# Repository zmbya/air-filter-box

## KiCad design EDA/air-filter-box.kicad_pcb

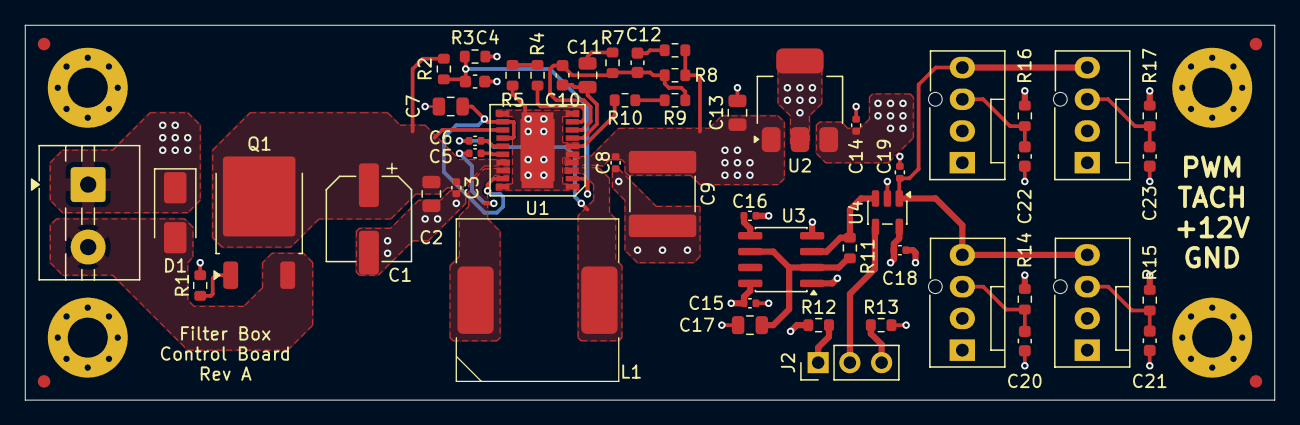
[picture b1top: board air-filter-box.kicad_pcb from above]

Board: 4 copper layers, 100.0 x 30.0 mm, 61 parts (0 on the bottom side), 30 nets.

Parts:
C1: 47u; CP_Elec_6.3x7.7
C2, C7, C13: 470n; C_0805_2012Metric
C3, C5, C6, C8, C14, C15, C16, C18, C19: 100n; C_0402_1005Metric
C4: 1n; C_0603_1608Metric
C9: 22u; C_2220_5750Metric
C10: 47p; C_0603_1608Metric
C11, C17: 2n2; C_0805_2012Metric
C12: 33p; C_0603_1608Metric
C20, C21, C22, C23: 1u; C_0603_1608Metric
D1: SMAJ26CA-13-F; D_SMA
FID1, FID2, FID3, FID4: Fiducial; Fiducial_1mm_Mask2mm
H1, H2, H3, H4: M3; MountingHole_3.2mm_M3_Pad_Via
J1: WJ128V-5.0-02P-14-00A; TerminalBlock_MaiXu_MX126-5.0-02P_1x02_P5.00mm
J2: Conn_01x03_Pin; PinHeader_1x03_P2.54mm_Vertical
J3, J4, J5, J6: Fan Header 4 Pin; FanPinHeader_1x04_P2.54mm_Vertical
L1: 10u; SMDRI127-XXX-12.3-12.3-8.0
Q1: TPM10030PK3; TO-252-2
R1: 100k; R_0603_1608Metric
R2, R8: 1M; R_0603_1608Metric
R3: 330k; R_0603_1608Metric
R4: 30k; R_0603_1608Metric
R5: 5k6; R_0603_1608Metric
R6, R7: 18k; R_0603_1608Metric
R9: 82k; R_0603_1608Metric
R10: 9k1; R_0603_1608Metric
R11: 12k; R_0603_1608Metric
R12, R13: 10k; R_0603_1608Metric
R14, R15, R16, R17: 1k; R_0603_1608Metric
U1: LTC3115EFE-1#PBF; 20-lead-tssop-ep-lts-05-08-1663-ca
U2: UA78M05CDCYR; SOT-223-3_TabPin2
U3: NE555DR; SOIC-8_3.9x4.9mm_P1.27mm
U4: TLV7031DBVR; SOT-23-5

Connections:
5-24V: C1.1, C2.1, C3.1, Q1.2 (D), R2.1, U1.13 (VIN), U1.17 (PVIN)
+5V: C14.1, C15.1, C18.1, R12.1, R14.1, R15.1, R16.1, R17.1, U2.3 (OUT), U3.4 (~RST), U3.8 (VCC), U4.5 (V+)
+12V: C8.1, C9.1, C13.1, J3.2, J4.2, J5.2, J6.2, R6.1, R8.1, U1.4 (PVOUT), U2.1 (IN)
/555-out: R11.1, U3.3 (OUT), U4.3 (+)
/FB: C10.2, C12.2, R7.2, R8.2, R9.1, U1.8 (FB)
/RT: R4.1, U1.9 (RT)
/RUN: C4.1, R2.2, R3.1, U1.2 (RUN)
/VC: C10.1, C11.1, U1.7 (VC)
/VIN: D1.2 (A2), J1.2, Q1.3 (S)
/ind-cap1: C5.2, U1.16 (BST1)
/ind-cap2: C6.2, U1.15 (BST2)
/ind-sw1: C5.1, L1.1, U1.18 (SW1)
/ind-sw2: C6.1, L1.2, U1.3 (SW2)
/pwm-pvcc-vcc: C7.1, U1.12 (VCC), U1.14 (PVCC), U1.19 (PWM/SYNC)
/threshold-trigger: C17.1, R11.2, U3.2 (TRIG), U3.6 (THRES)
GND: C1.2, C2.2, C3.2, C4.2, C7.2, C8.2, C9.2, C13.2, C14.2, C15.2, C16.2, C17.2, C18.2, C19.2, C20.2, C21.2, C22.2, C23.2, D1.1 (A1), H1.1 (1_1), H2.1 (1_1), H3.1 (1_1), H4.1 (1_1), J1.1, J3.1, J4.1, J5.1, J6.1, R1.2, R3.2, R5.2, R10.2, R13.2, U1.1 (PGND), U1.5 (GND), U1.6 (GND), U1.10 (PGND), U1.11 (PGND), U1.20 (PGND), U1.21 (PGND), U2.2 (GND), U3.1 (GND), U4.2 (V-)
unnamed: C11.2, R7.1
unnamed: C12.1, R6.2
unnamed: J2.1, R12.2
unnamed: J2.2, U4.4 (-)
unnamed: J2.3, R13.1
unnamed: Q1.1 (G), R1.1
unnamed: R4.2, R5.1
unnamed: R9.2, R10.1
unnamed: C16.1, U3.5 (CONT)
PWM: C19.1, J3.4, J4.4, J5.4, J6.4, U4.1
TACH1: C20.1, J3.3, R14.2
TACH2: C22.1, J4.3, R16.2
TACH3: C21.1, J5.3, R15.2
TACH4: C23.1, J6.3, R17.2
